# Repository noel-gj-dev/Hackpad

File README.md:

# Hackpad
Hackpad is a 3 key macropad with a rotary encoder. It also has 1 SK6812 MINI-E LED, and uses KMK firmware.

# Features:
<ul>
  <li>EC11 Rotary encoder for whatever you want (personaly i will use it for a volume knob)</li>
  <li>1 SK6812 MINI-E LED</li>
  <li>3 Switches/Keys for any purpose you want</li>
</ul>

# CAD Model:
Everything fits together using 4 M3x16mm Bolts and M3x5mx4mm heatset inserts for the case.

It has 2 separate printed pieces. The base where the PCB sits and the top cover.

Made in Fusion360.

# PCB:
Here's my PCB! It was made in KiCad.

Schematic:<br>

PCB:<br>

# Firmware
This hackpad uses KMK firmware for everything.

<ul>
  <li>The rotary encoder changes volume. Press to play/pause.</li>
  <li>The 3 keys currently type 1, 2 and 3. However I can dynamically change the code.</li>
  <li>The mini LED is just ON as a static light with a red color.</li>
</ul>

# BOM:
Here is everything you need to make this hackpad.

<ul>
  <li>3x Cherry MX Switches</li>
  <li>3x DSA Keycaps</li>
  <li>1x EC11 Rotary encoder</li>
  <li>1x SK6812 MINI-E LED</li>
  <li>1x Seeed XIAO RP2040</li>
  <li>4x M3x5x4 Heatset inserts</li>
  <li>4x M3x16mm Screws</li>
  <li>1x Case (two 3D printed parts, the base where the PCB sits and the top cover)</li>
</ul>

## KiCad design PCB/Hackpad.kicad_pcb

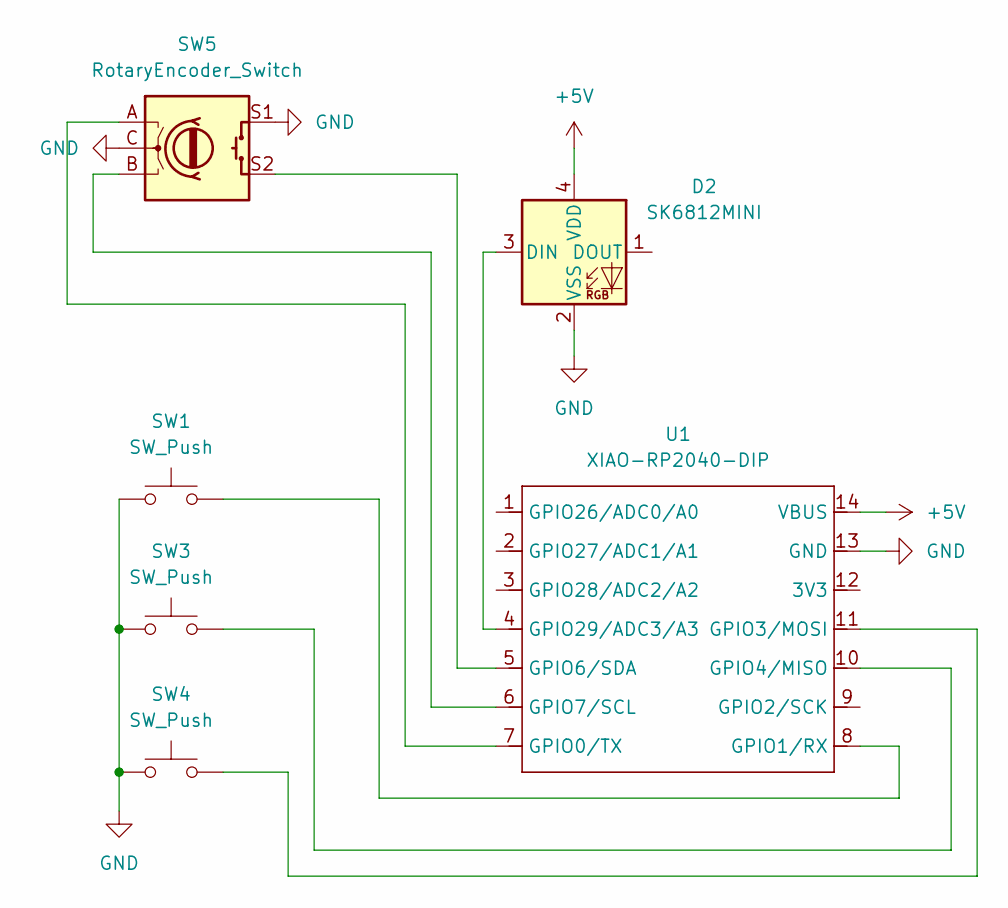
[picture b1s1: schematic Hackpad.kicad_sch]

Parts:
D2: SK6812MINI; LED_SK6812MINI_PLCC4_3.5x3.5mm_P1.75mm
SW1, SW3, SW4: SW_Push; SW_Cherry_MX_1.00u_PCB
SW5: RotaryEncoder_Switch; RotaryEncoder_Alps_EC11E-Switch_Vertical_H20mm
U1: XIAO-RP2040-DIP

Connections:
+5V: D2.4 (VDD), U1.14 (VBUS)
GND: D2.2 (VSS), SW1.1, SW3.1, SW4.1, SW5.C, SW5.S1, U1.13 (GND)
unnamed: D2.3 (DIN), U1.4 (GPIO29/ADC3/A3)
unnamed: SW5.A, U1.7 (GPIO0/TX)
unnamed: SW1.2, U1.8 (GPIO1/RX)
unnamed: SW4.2, U1.11 (GPIO3/MOSI)
unnamed: SW3.2, U1.10 (GPIO4/MISO)
unnamed: SW5.S2, U1.5 (GPIO6/SDA)
unnamed: SW5.B, U1.6 (GPIO7/SCL)

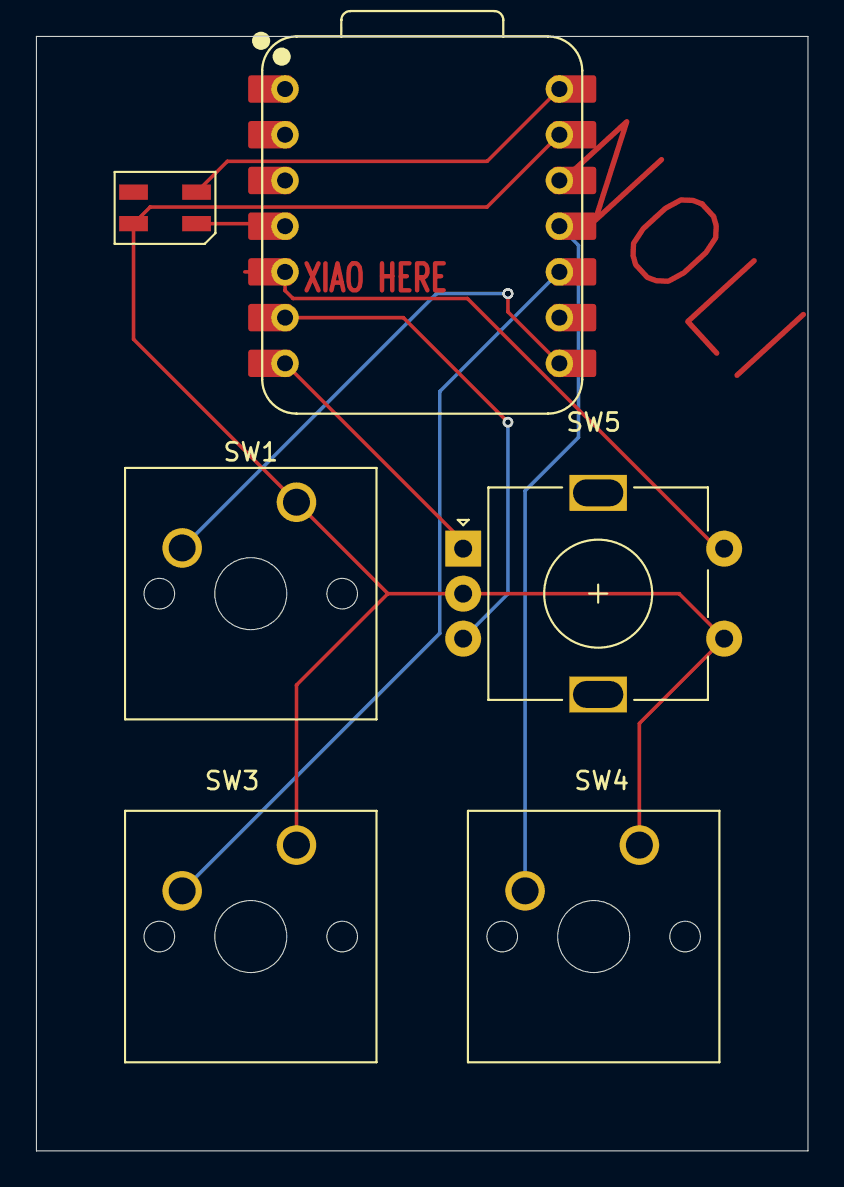
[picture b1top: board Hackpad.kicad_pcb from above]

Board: 2 copper layers, 42.9 x 61.9 mm, 6 parts (0 on the bottom side), 9 nets.
